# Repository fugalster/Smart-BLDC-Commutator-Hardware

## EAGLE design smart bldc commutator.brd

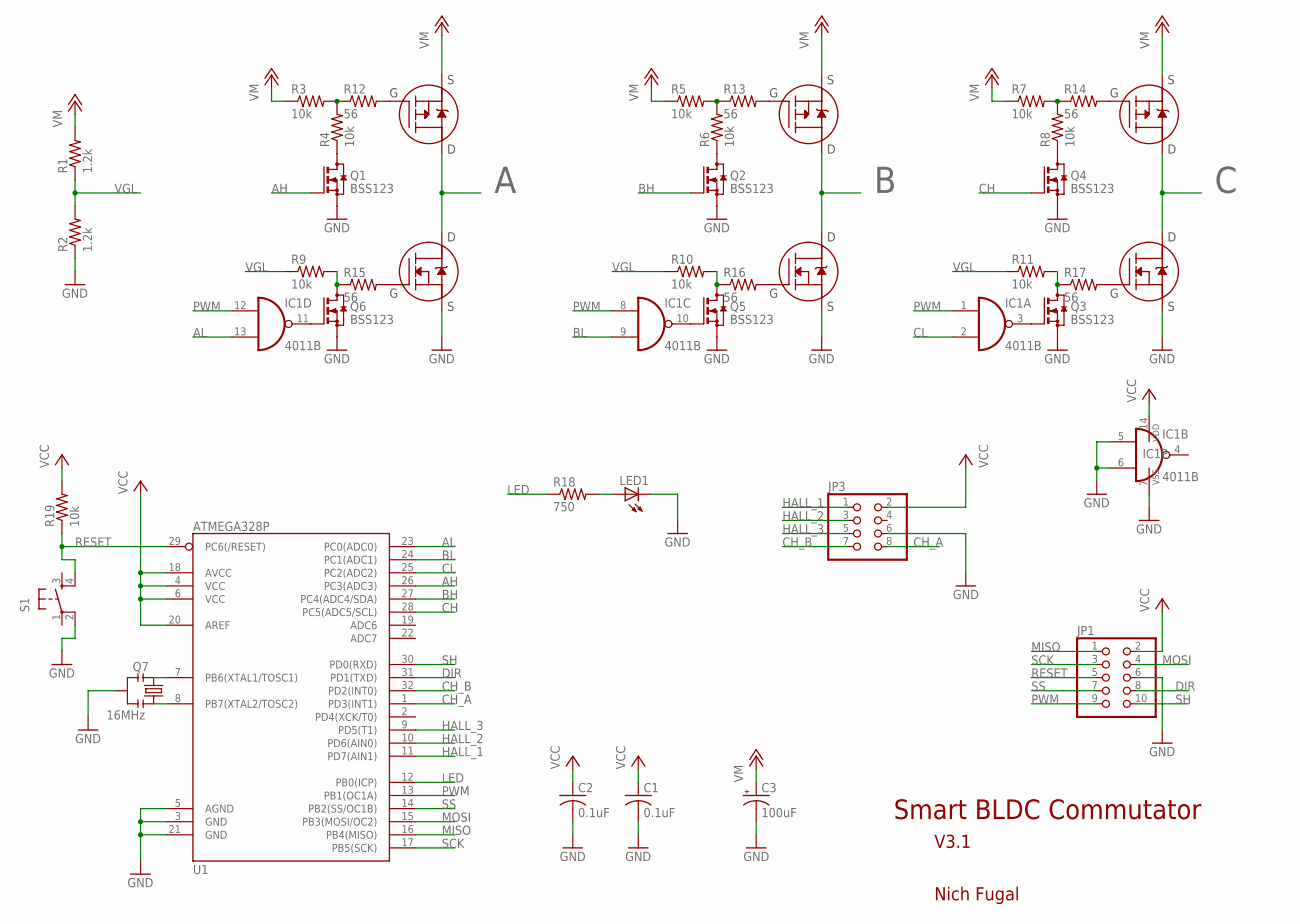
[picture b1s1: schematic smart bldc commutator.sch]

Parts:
C1, C2: 0.1uF; C0805
C3: 100uF; E3,5-8
IC1: 4011B; SO14
JP1: PINHD-2X5; 2X05
JP3: PINHD-2X4; 2X04
LED1: LEDCHIP-LED0805; CHIP-LED0805
Q1, Q2, Q3, Q4, Q5, Q6: BSS123; SOT23
Q7: 16MHz; RESONATOR-SMD
R1, R2: 1.2k; R0805
R3, R4, R5, R6, R7, R8, R9, R10, R11, R19: 10k; R0805
R12, R13, R14, R15, R16, R17: 56; R0805
R18: 750; R0805
S1: TAC_SWITCHSMD; TACTILE_SWITCH_SMD
U1: ATMEGA328P; TQFP32-08
U$1, U$3, U$5: IRF4905; D2PAK
U$2, U$4, U$6: IRF1404S; D2PAK

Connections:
A: U$1.2 (D), U$2.2 (D)
AH: Q1.1 (G), U1.26 (PC3(ADC3))
AL: IC1.13 (I1), U1.23 (PC0(ADC0))
B: U$3.2 (D), U$4.2 (D)
BH: Q2.1 (G), U1.27 (PC4(ADC4/SDA))
BL: IC1.9 (I1), U1.24 (PC1(ADC1))
C: U$5.2 (D), U$6.2 (D)
CH: Q4.1 (G), U1.28 (PC5(ADC5/SCL))
CH_A: JP3.8, U1.1 (PD3(INT1))
CH_B: JP3.7, U1.32 (PD2(INT0))
CL: IC1.2 (I1), U1.25 (PC2(ADC2))
DIR: JP1.8, U1.31 (PD1(TXD))
GND: C1.2, C2.2, C3.-, IC1.5 (I0), IC1.6 (I1), IC1.7 (VSS), JP1.6, JP3.6, LED1.C, Q1.2 (S), Q2.2 (S), Q3.2 (S), Q4.2 (S), Q5.2 (S), Q6.2 (S), Q7.2, R2.1, S1.2, U1.3 (GND), U1.5 (AGND), U1.21 (GND), U$2.3 (S), U$4.3 (S), U$6.3 (S)
HALL_1: JP3.1, U1.11 (PD7(AIN1))
HALL_2: JP3.3, U1.10 (PD6(AIN0))
HALL_3: JP3.5, U1.9 (PD5(T1))
LED: R18.1, U1.12 (PB0(ICP))
MISO: JP1.1, U1.16 (PB4(MISO))
MOSI: JP1.4, U1.15 (PB3(MOSI/OC2))
unnamed: Q7.3, U1.7 (PB6(XTAL1/TOSC1))
unnamed: Q7.1, U1.8 (PB7(XTAL2/TOSC2))
unnamed: Q6.3 (D), R9.2, R15.1
unnamed: R12.2, U$1.1 (G)
unnamed: Q5.3 (D), R10.2, R16.1
unnamed: Q4.3 (D), R8.1
unnamed: R15.2, U$2.1 (G)
unnamed: R3.2, R4.2, R12.1
unnamed: R13.2, U$3.1 (G)
unnamed: R14.2, U$5.1 (G)
unnamed: R5.2, R6.2, R13.1
unnamed: Q3.3 (D), R11.2, R17.1
unnamed: IC1.3 (O), Q3.1 (G)
unnamed: Q2.3 (D), R6.1
unnamed: R16.2, U$4.1 (G)
unnamed: R17.2, U$6.1 (G)
unnamed: R7.2, R8.2, R14.1
unnamed: LED1.A, R18.2
unnamed: IC1.10 (O), Q5.1 (G)
unnamed: Q1.3 (D), R4.1
unnamed: IC1.11 (O), Q6.1 (G)
PWM: IC1.1 (I0), IC1.8 (I0), IC1.12 (I0), JP1.9, U1.13 (PB1(OC1A))
RESET: JP1.5, R19.1, S1.4, U1.29 (PC6(/RESET))
SCK: JP1.3, U1.17 (PB5(SCK))
SH: JP1.10, U1.30 (PD0(RXD))
SS: JP1.7, U1.14 (PB2(SS/OC1B))
VCC: C1.1, C2.1, IC1.14 (VDD), JP1.2, JP3.2, R19.2, U1.4 (VCC), U1.6 (VCC), U1.18 (AVCC), U1.20 (AREF)
VGL: R1.1, R2.2, R9.1, R10.1, R11.1
VM: C3.+, R1.2, R3.1, R5.1, R7.1, U$1.3 (S), U$3.3 (S), U$5.3 (S)

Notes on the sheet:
V3.1
Nich Fugal
Smart BLDC Commutator

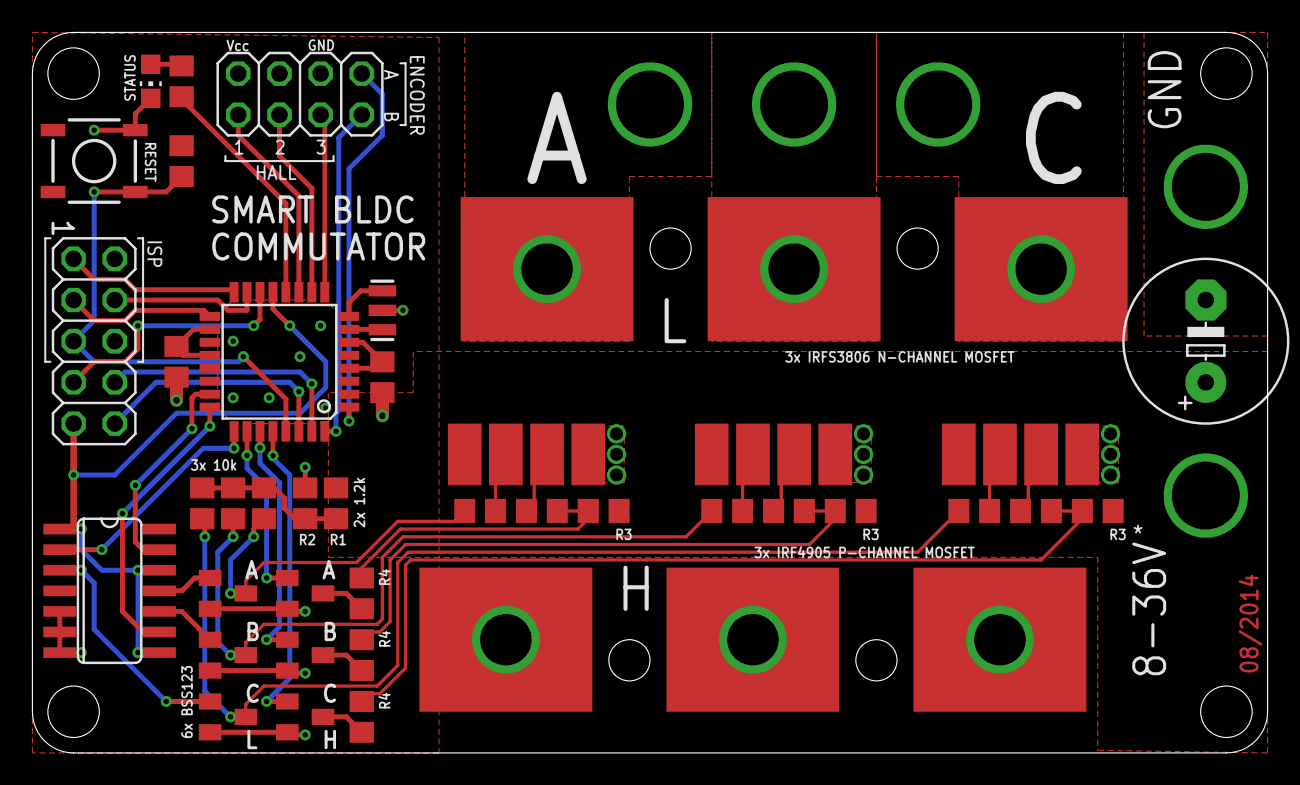
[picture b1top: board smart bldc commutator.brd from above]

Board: 2 copper layers, 76.2 x 44.5 mm, 41 parts (0 on the bottom side), 48 nets.

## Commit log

2014-08-08 :lollipop: Added .gitattributes & .gitignore files
2014-08-08 Added design files
2014-08-08 Updated .gitignore
2014-08-08 Fixed +12V to VM label in schematic
2014-08-19 Added alternate stencil design and BOM
2014-09-02 Updated large capacitor to 50V model
2014-09-02 deleted extra files
2014-09-08 V3.2 Hardware
    Minor changes to silkscreen and bottom layer polygons.
2014-09-08 V3.2 Hardware
    Updated images to match
2014-09-08 V3.2 Hardware
    One more update

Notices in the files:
parts and their libraries:
sparkfun: Licensing: CC v3.0 Share-Alike You are welcome to use this library for commercial purposes.
